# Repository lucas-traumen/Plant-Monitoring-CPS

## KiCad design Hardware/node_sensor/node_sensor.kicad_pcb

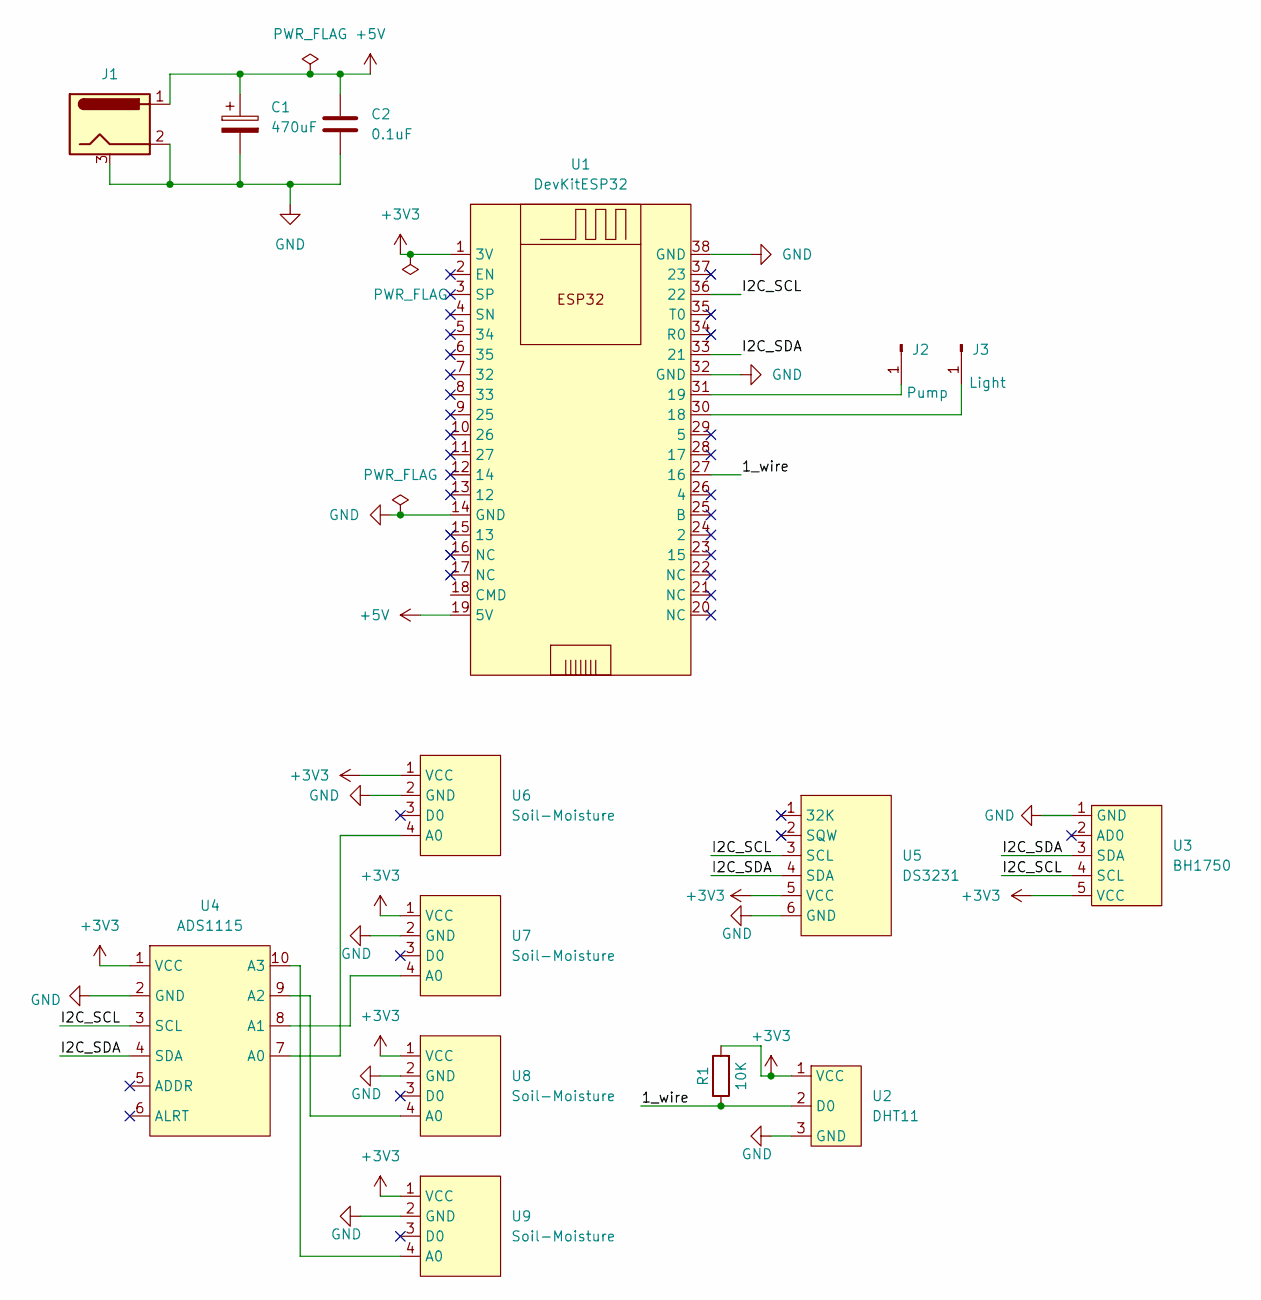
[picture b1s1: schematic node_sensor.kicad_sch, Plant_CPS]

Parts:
C1: 470uF; C_Radial_D8.0mm_H11.5mm_P3.50mm
C2: 0.1uF; C_Disc_D3.0mm_W1.6mm_P2.50mm
J1: Conn_Jack-DC; BarrelJack_Horizontal
J2: Pump; PinHeader_1x01_P1.00mm_Vertical
J3: Light; PinHeader_1x01_P1.00mm_Vertical
R1: 10K; R_Axial_DIN0207_L6.3mm_D2.5mm_P10.16mm_Horizontal
U1: DevKitESP32; ESP32-DevKitC
U2: DHT11; JST_XH_B3B-XH-A_1x03_P2.50mm_Vertical
U3: BH1750; JST_XH_B5B-XH-A_1x05_P2.50mm_Vertical
U4: ADS1115; PinSocket_1x10_P2.54mm_Vertical
U5: DS3231; PinSocket_1x06_P2.54mm_Vertical
U6, U7, U8, U9: Soil-Moisture; Conn_XH-P2.54mm-4P

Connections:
+3V3: R1.2, U1.1 (3V), U2.1 (VCC), U3.5 (VCC), U4.1 (VCC), U5.5 (VCC), U6.1 (VCC), U7.1 (VCC), U8.1 (VCC), U9.1 (VCC)
+5V: C1.1, C2.1, J1.1, U1.19 (5V)
/1_wire: R1.1, U1.27 (16), U2.2 (D0)
/I2C_SCL: U1.36 (22), U3.4 (SCL), U4.3 (SCL), U5.3 (SCL)
/I2C_SDA: U1.33 (21), U3.3 (SDA), U4.4 (SDA), U5.4 (SDA)
GND: C1.2, C2.2, J1.2, J1.3, U1.14 (GND), U1.32 (GND), U1.38 (GND), U2.3 (GND), U3.1 (GND), U4.2 (GND), U5.6 (GND), U6.2 (GND), U7.2 (GND), U8.2 (GND), U9.2 (GND)
unnamed: J2.1 (Pin_1_1), U1.31 (19)
unnamed: J3.1 (Pin_1_1), U1.30 (18)
unnamed: U4.7 (A0), U6.4 (A0)
unnamed: U4.8 (A1), U7.4 (A0)
unnamed: U4.9 (A2), U8.4 (A0)
unnamed: U4.10 (A3), U9.4 (A0)

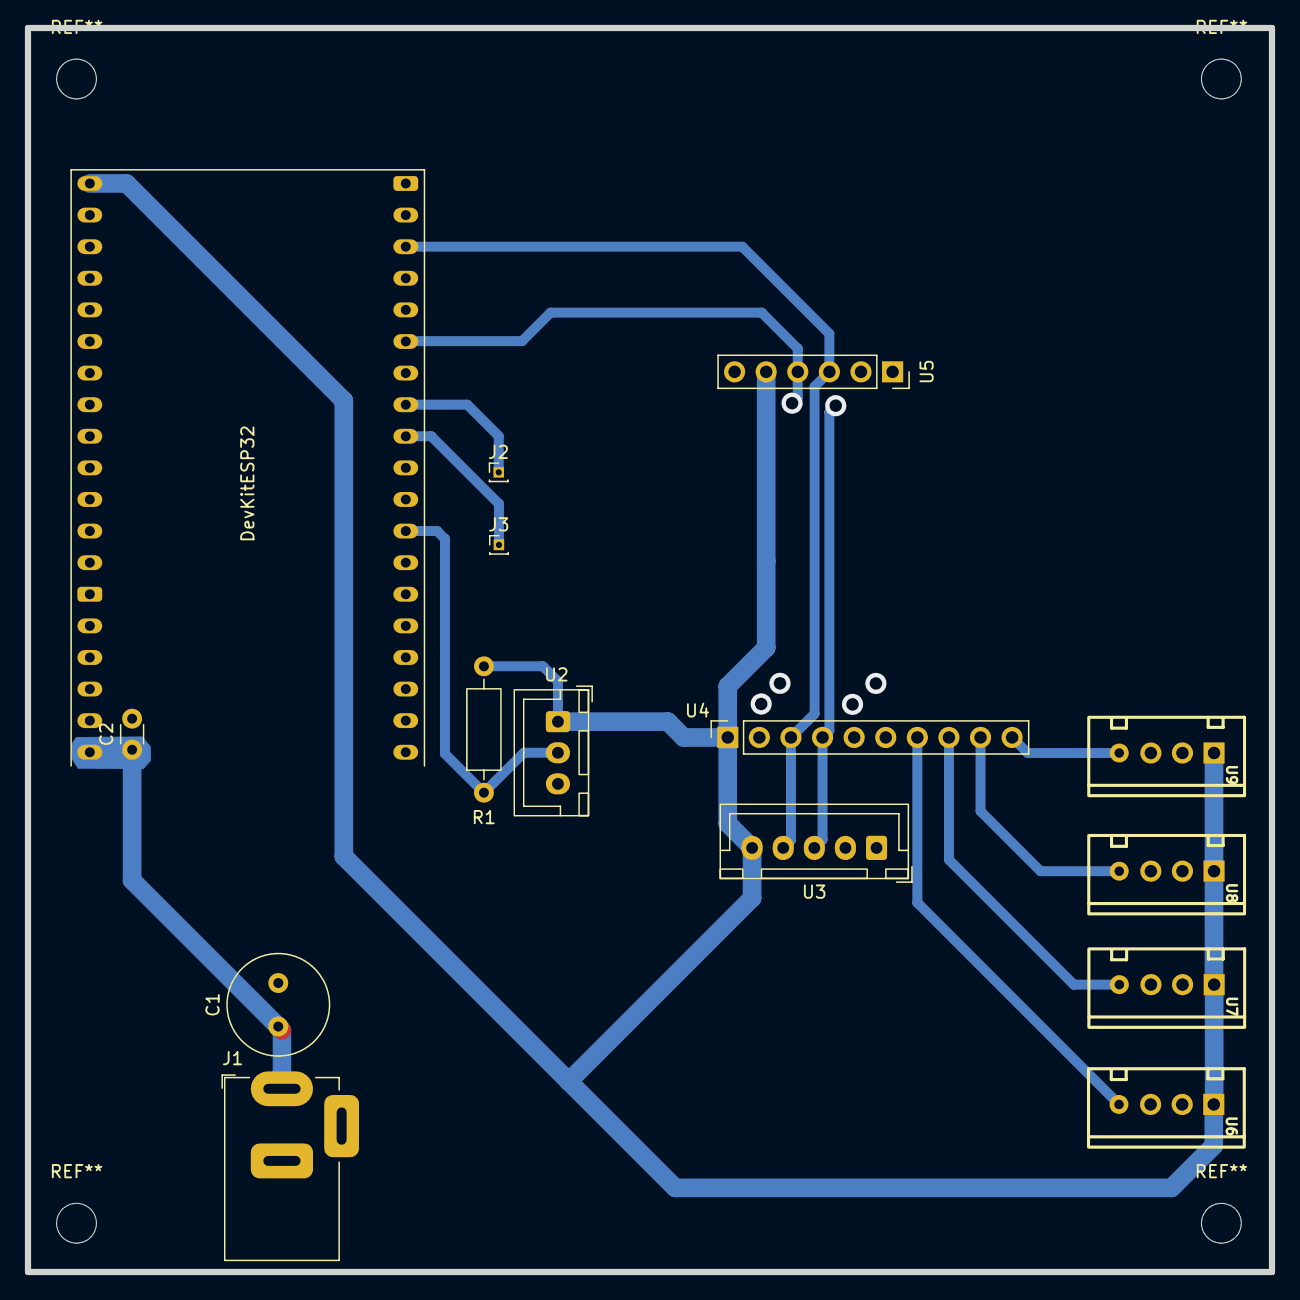
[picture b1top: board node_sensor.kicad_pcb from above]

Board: 2 copper layers, 100.0 x 100.0 mm, 15 parts (0 on the bottom side), 12 nets.

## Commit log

2026-05-19 removed to handle the pump at edge
2026-05-24 constructed all project
2026-05-24 rm write log in BBB
2026-05-26 "fix rebase"
2026-05-26 updated flow DT
2026-05-27 fixed spam control
2026-06-01 add clean web dashboard for BBB gateway flow
2026-06-09 change topic - switch pi 4
2026-06-09 change topic -esp32
2026-06-12 updated pcb
2026-06-16 fusion-sensor,check nvs-DB
2026-06-16 changed flow data
2026-06-17 change flow data
2026-06-17 modified flow backend-web
2026-06-17 fixed delay - wrong hostpot
